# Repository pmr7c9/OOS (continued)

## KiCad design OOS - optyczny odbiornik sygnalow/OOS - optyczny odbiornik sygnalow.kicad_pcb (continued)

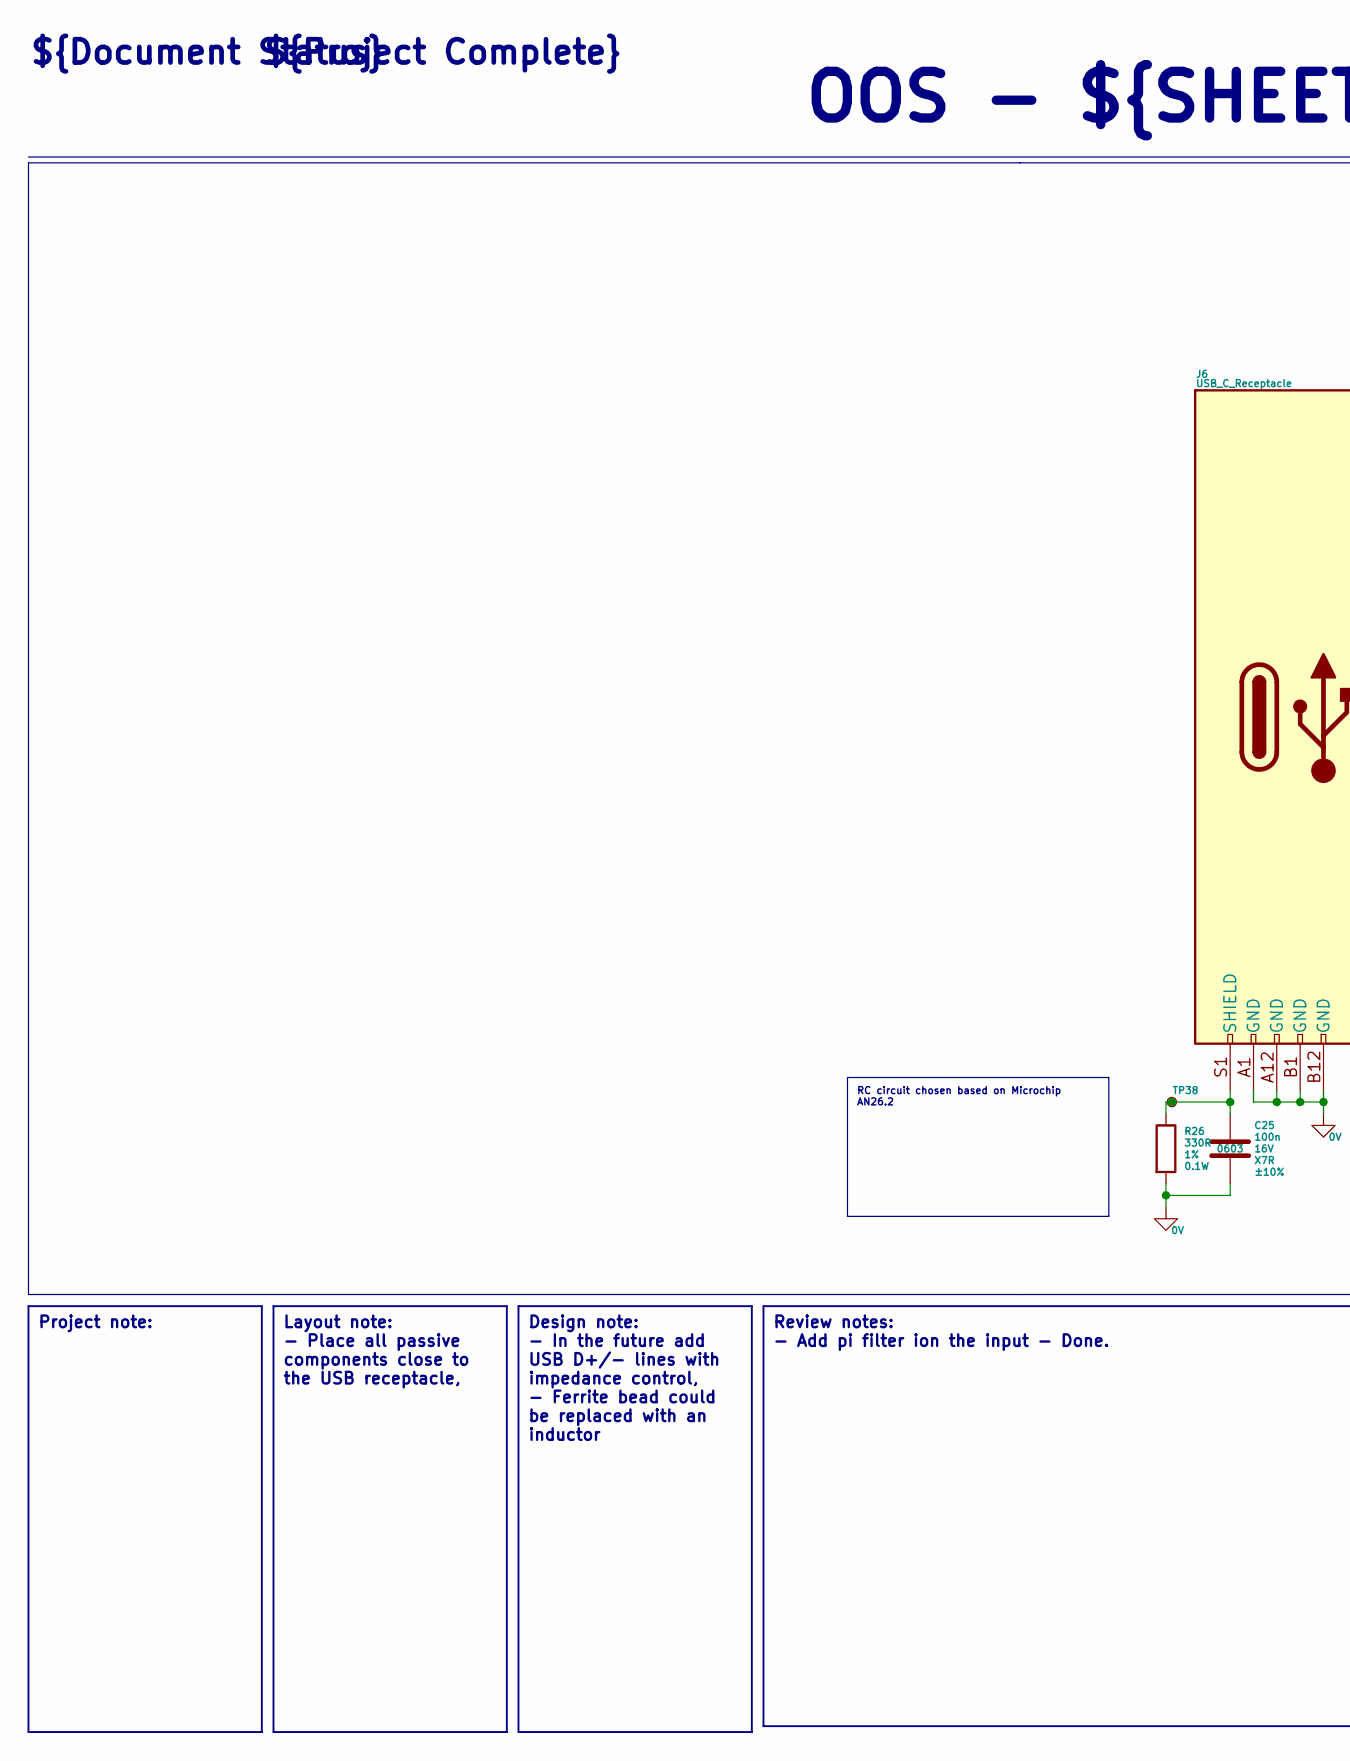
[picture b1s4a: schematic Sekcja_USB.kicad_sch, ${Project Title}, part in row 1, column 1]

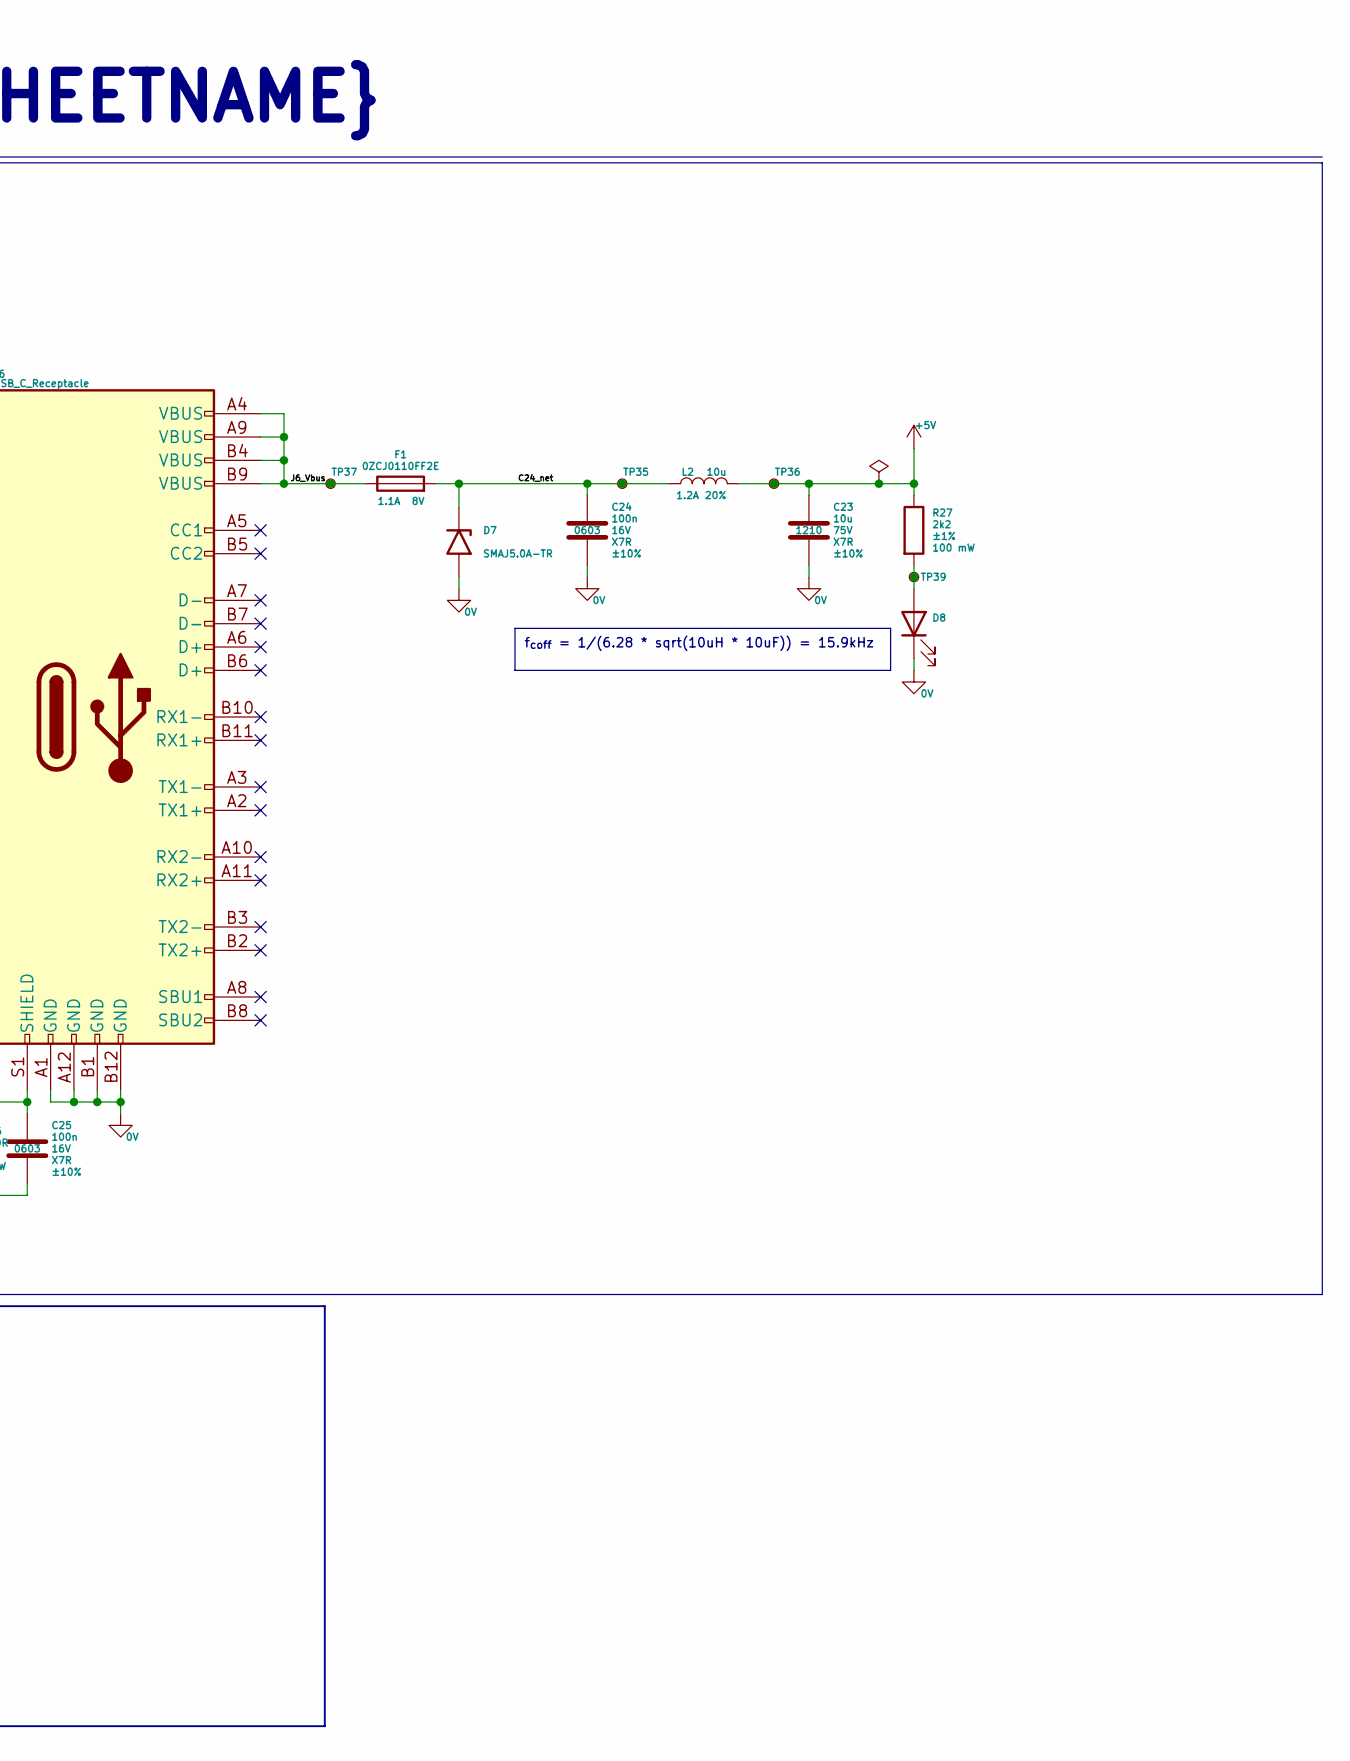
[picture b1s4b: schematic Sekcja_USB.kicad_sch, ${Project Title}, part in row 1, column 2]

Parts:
C23: 10u; C_1210_3225Metric_Pad1.33x2.70mm_HandSolder; Voltage Rating 75V; Tolerance ±10%
C24, C25: 100n; C_0603_1608Metric_Pad1.08x0.95mm_HandSolder; Voltage Rating 16V; Tolerance ±10%; MPN CL10B104KO8WPNC
D7: SMAJ5.0A-TR; D_SMA_Handsoldering
D8: LED; D_0603_1608Metric_Pad1.05x0.95mm_HandSolder; MPN LTST-C191KGKT
F1: 0ZCJ0110FF2E; Fuse_1206_3216Metric; Max Voltage 8V
J6: USB_C_Receptacle; USB_C_Receptacle_Amphenol_12401548E4-2A
L2: 10u; L_Vishay_IHLP-1212; Tolerance 20%
R26: 330R; R_0603_1608Metric; Power Rating 0.1W; Tolerance 1%
R27: 2k2; R_0603_1608Metric_Pad0.98x0.95mm_HandSolder; Power Rating 100 mW; Tolerance ±1%; MPN AC0603FR-072K2L
TP35, TP36, TP37, TP38, TP39: TestPoint_Small; TestPoint_Pad_D1.0mm

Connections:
0V: C23.2, C24.2, C25.2, D7.2 (A2), D8.1 (K), J6.A1 (GND), J6.A12 (GND), J6.B1 (GND), J6.B12 (GND), R26.2; also elsewhere on the board
+5V: C23.1, L2.2, R27.1, TP36.1; also elsewhere on the board
/Sekcja_USB/C24_net: C24.1, D7.1 (A1), F1.2, L2.1, TP35.1
/Sekcja_USB/J6_Vbus: F1.1, J6.A4 (VBUS), J6.A9 (VBUS), J6.B4 (VBUS), J6.B9 (VBUS), TP37.1
unnamed: D8.2 (A), R27.2, TP39.1
unnamed: C25.1, J6.S1 (SHIELD), R26.1, TP38.1

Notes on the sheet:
${Project Complete}
OOS - ${SHEETNAME}
${Document Status}
Review notes: - Add pi filter ion the input - Done.
Layout note: - Place all passive components close to the USB receptacle,
f_{coff} = 1/(6.28 * sqrt(10uH * 10uF)) = 15.9kHz
Project note:
Design note: - In the future add USB D+/- lines with impedance control, - Ferrite bead could be replaced with an inductor
RC circuit chosen based on Microchip AN26.2

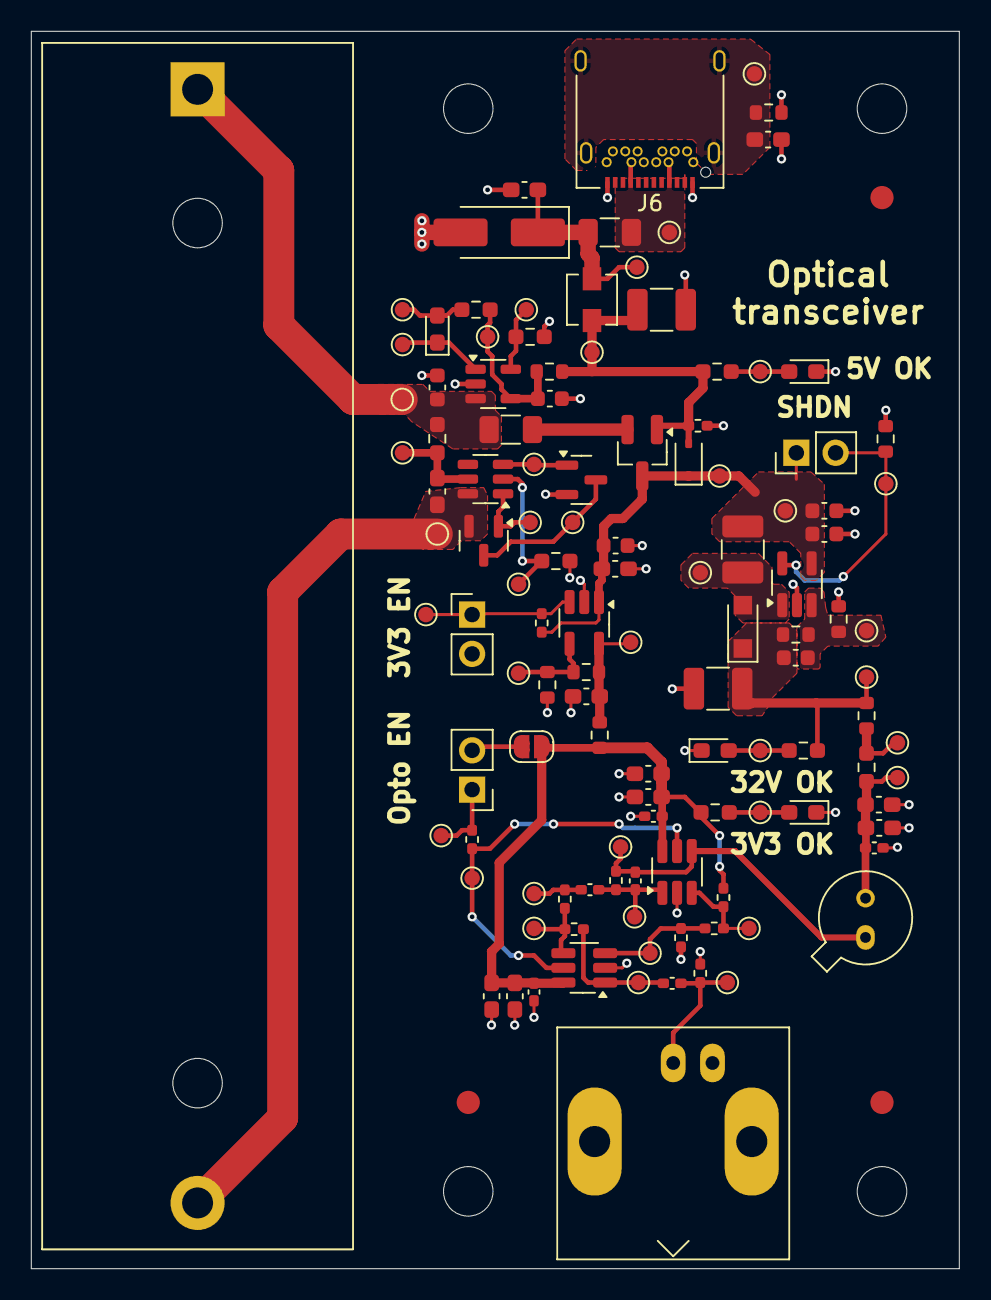
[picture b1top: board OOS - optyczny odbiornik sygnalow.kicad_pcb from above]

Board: 2 copper layers, 60.0 x 80.0 mm, 126 parts (0 on the bottom side), 41 nets.

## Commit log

2025-05-22 Solved points from review on page OOS - Analog Part2
2025-05-28 Add Charging, protection circuit and LDO for +3V3 with passive, transistor and diode components
2025-05-30 Finish Li-Lion section, add for review
2025-05-30 Adding review notes for Li-ion battery schematic
2025-05-30 Internal changes
2025-05-30 Implementing changes after review on Li-Ion section, adding components to USB section
2025-05-31 Adding Pi ferrite beat for PI filter on USB, changing RC values for SHIELD pin
2025-05-31 Adding calciulations for PI filter, moving PI filter after the fuse, replacing ferrite bead with inductor
2025-06-03 Changing the inductor at USB Pi filter for higher current. Changing the capacitors as well so cutoff frequency is around 15 kHz
2025-06-03 Creating layout branch, creating a blank pcb file and creating constraints based on JLC PCB capabilities from their website. To every capability lsited a small margin has been added in project constr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
2025-06-04 Changing the PI filter, now before inductor we have 10uF and after 100nF capacitors. Inductor itself was not changed
2025-06-04 Adding max board dimentions possible to get 2$ PCBs from JLCPCB. Dimentions will be shrunk as the components are being placed
2025-06-05 Clean schematic, what left is to add resistors for pull down on usb page and rotary switch on analog page
2025-06-10 All sections except analog are placed (initial placement) on the PCB. Routing not started yet.
2025-06-11 Initial component placement is done. Rotary switch needs to be added and a 4th mount hole placed or removed (to be decided). When selecting resistors for the rotary switch please consider 0402 case d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
2025-06-11 Changing the placement - opamps closer to photodiode, passive components closer to ICs like DCDC converter, Linear 3v3 converter. SHDN resistor moved further away from DCDC and will be routed on the 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
2025-06-11 repeated push
2025-06-11 making opto circuit much tighter
2025-06-11 Move testpoint TP37
2025-06-11 Added polygon for USB3.2, move TP37 on a schematic
2025-06-11 Moved TP37 on schematic, Added LED diode with resistor for +5V indication, improved component placement for USB3.2
2025-06-11 Add netclass on schematic and pcb
2025-06-12 trying a different placement for components
2025-06-12 Change on charger side, moved components and place tracks and vias
2025-06-12 Place, route, adjust tracks and components for charger and balancer, create groups
2025-11-27 Zrobiono placement oraz routing. Nalezy jeszcze dodac przelotki do gnd blisko pinow na top layer
2025-11-27 Layout finished, need to turn off constraints for USB (J6)
2025-11-28 Zrobiony nieco lepszy layout
2025-11-28 Dodane napisy na jumperach
2026-04-22 Add description for OOS device in README
    Added a description of the optical signal receiver device.
2026-04-22 Fix formatting in README.md
